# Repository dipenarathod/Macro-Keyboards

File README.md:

# Macro-Keyboards
Pending and completed macro keyboards:
1)Macro Keyboard: Pending, uses Atmega 32u4
2)MacroKeyboard2: Completed, uses push-buttons
3)MacroKeyboard2RotaryEncoders_Mech_with_profiles: Completed, uses LEDs for profiles and has Cherry MX switches
4)MacroKeyboardOLED: PCB pending, will have Cherry MX switches and an SSD1306
5)ModdedCrown.pretty: Crown logo for PCB

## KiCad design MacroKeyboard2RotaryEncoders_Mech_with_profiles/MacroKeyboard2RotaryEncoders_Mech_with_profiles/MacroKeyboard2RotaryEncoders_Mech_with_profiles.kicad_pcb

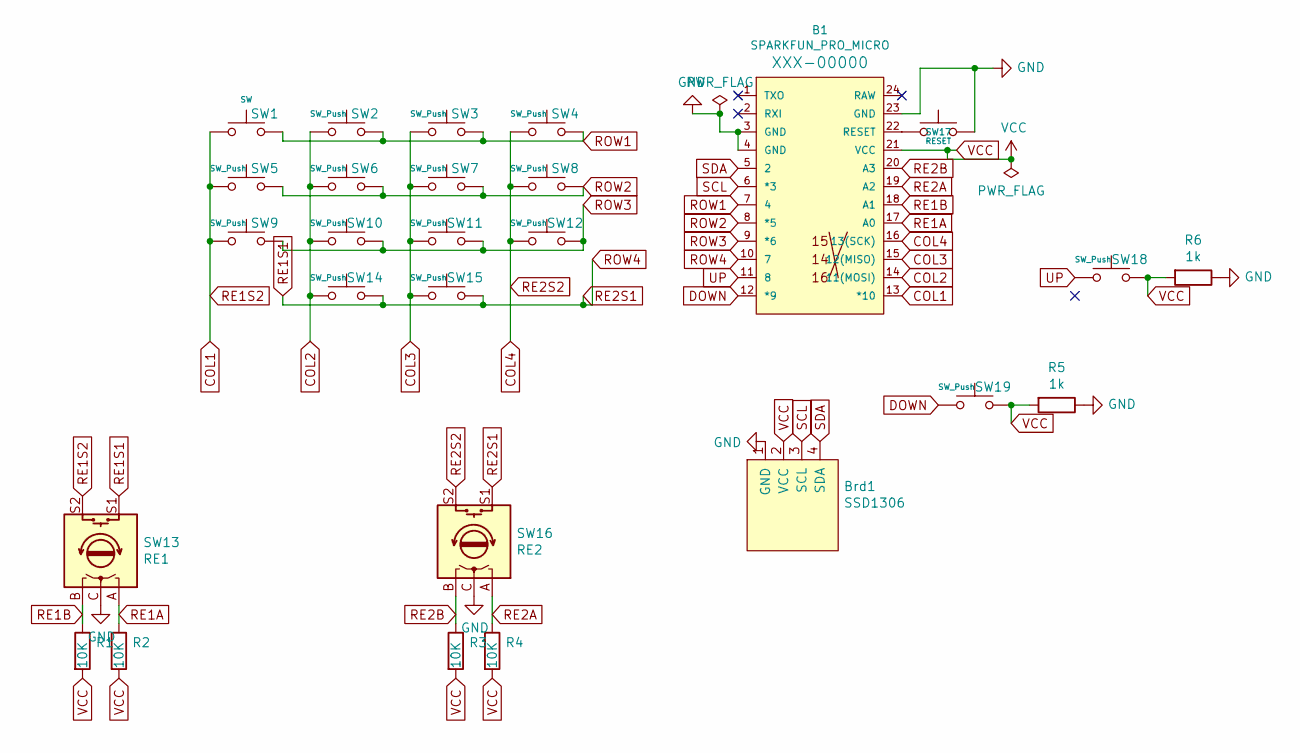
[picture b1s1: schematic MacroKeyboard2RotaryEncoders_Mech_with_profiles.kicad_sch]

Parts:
B1: SPARKFUN_PRO_MICRO
Brd1: SSD1306; 128x64OLED
R1, R2, R3, R4: 10K; R_Axial_DIN0204_L3.6mm_D1.6mm_P5.08mm_Horizontal
R5, R6: 1k; R_Axial_DIN0204_L3.6mm_D1.6mm_P5.08mm_Horizontal
SW1: SW; SW_Cherry_MX_1.00u_Plate
SW2, SW3, SW4, SW5, SW6, SW7, SW8, SW9, SW10, SW11, SW12, SW14, SW15: SW_Push; SW_Cherry_MX_1.00u_Plate
SW13: RE1; RotaryEncoder_Alps_EC11E-Switch_Vertical_H20mm
SW16: RE2; RotaryEncoder_Alps_EC11E-Switch_Vertical_H20mm
SW17: RESET; SW_PUSH_6mm_H4.3mm
SW18, SW19: SW_Push; SW_PUSH_6mm_H4.3mm

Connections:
COL1: B1.13 (*10), SW1.1, SW5.1, SW9.1, SW13.S2
COL2: B1.14 (11(MOSI)), SW2.1, SW6.1, SW10.1, SW14.1
COL3: B1.15 (12(MISO)), SW3.1, SW7.1, SW11.1, SW15.1
COL4: B1.16 (13(SCK)), SW4.1, SW8.1, SW12.1, SW16.S2
DOWN: B1.12 (*9), SW19.1
GND: B1.3 (GND), B1.4 (GND), B1.23 (GND), Brd1.1 (GND), R5.1, R6.1, SW13.C, SW16.C, SW17.2
unnamed: B1.22 (RESET), SW17.1
RE1A: B1.17 (A0), R2.1, SW13.A
RE1B: B1.18 (A1), R1.1, SW13.B
RE1S1: B1.10 (7), SW13.S1, SW14.2, SW15.2, SW16.S1
RE2A: B1.19 (A2), R4.1, SW16.A
RE2B: B1.20 (A3), R3.1, SW16.B
ROW1: B1.7 (4), SW1.2, SW2.2, SW3.2, SW4.2
ROW2: B1.8 (*5), SW5.2, SW6.2, SW7.2, SW8.2
ROW3: B1.9 (*6), SW9.2, SW10.2, SW11.2, SW12.2
SCL: B1.6 (*3), Brd1.3 (SCL)
SDA: B1.5 (2), Brd1.4 (SDA)
UP: B1.11 (8), SW18.1
VCC: B1.21 (VCC), Brd1.2 (VCC), R1.2, R2.2, R3.2, R4.2, R5.2, R6.2, SW18.2, SW19.2

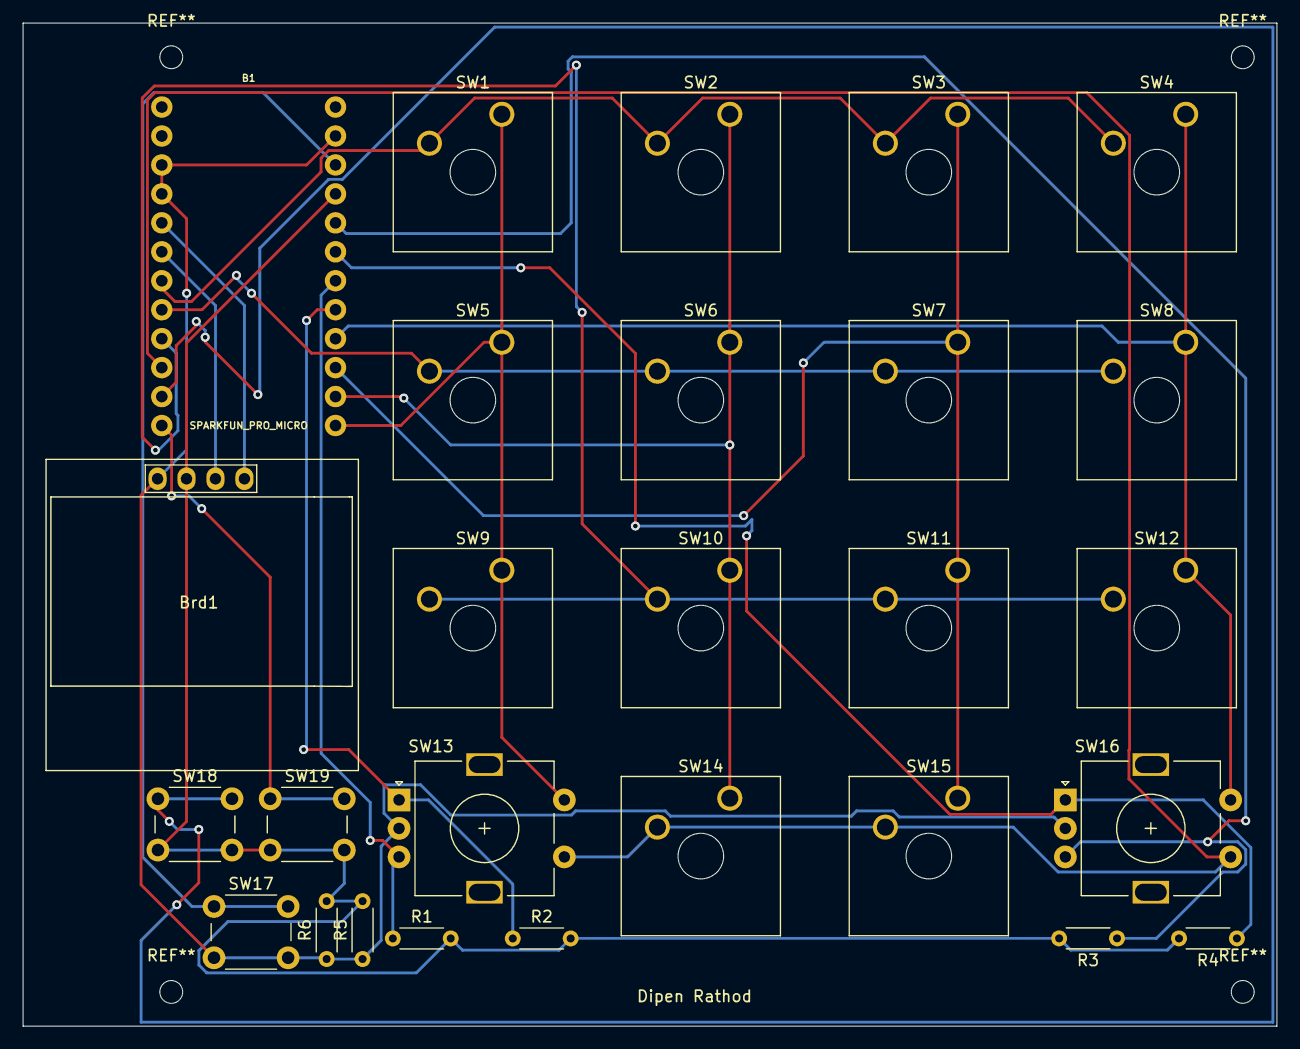
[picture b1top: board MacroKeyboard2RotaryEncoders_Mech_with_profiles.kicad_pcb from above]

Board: 2 copper layers, 110.0 x 88.0 mm, 27 parts (0 on the bottom side), 19 nets.

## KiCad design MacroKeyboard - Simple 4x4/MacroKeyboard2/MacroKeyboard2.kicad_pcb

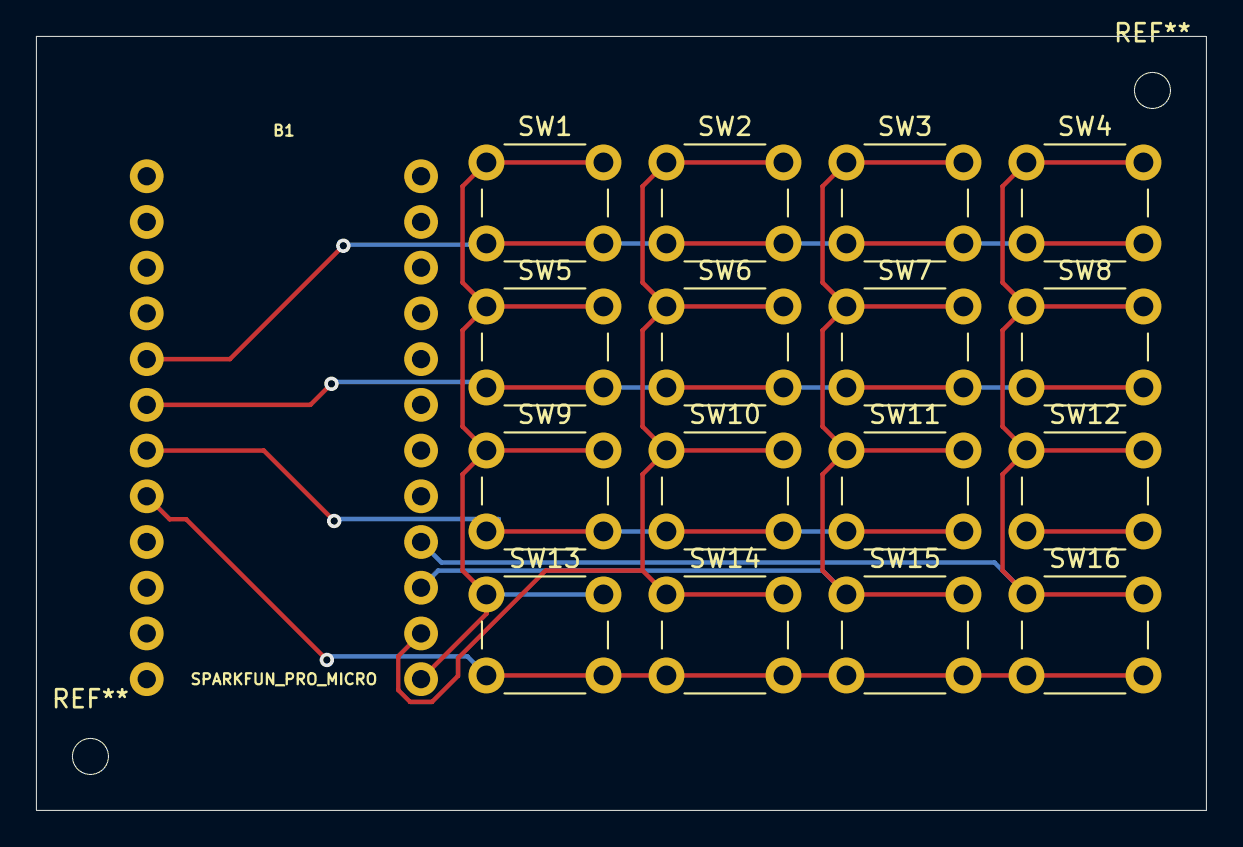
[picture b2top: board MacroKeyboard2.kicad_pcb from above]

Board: 2 copper layers, 65.0 x 43.0 mm, 17 parts (0 on the bottom side), 8 nets.

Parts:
B1: SPARKFUN_PRO_MICRO
SW1: SW; SW_PUSH_6mm_H4.3mm
SW2, SW3, SW4, SW5, SW6, SW7, SW8, SW9, SW10, SW11, SW12, SW13, SW14, SW15, SW16: SW_Push; SW_PUSH_6mm_H4.3mm

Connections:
unnamed: B1.5, SW1.2, SW2.2, SW3.2, SW4.2
unnamed: B1.6, SW5.2, SW6.2, SW7.2, SW8.2
unnamed: B1.7, SW9.2, SW10.2, SW11.2, SW12.2
unnamed: B1.8, SW13.2, SW14.2, SW15.2, SW16.2
unnamed: B1.13, SW1.1, SW5.1, SW9.1, SW13.1
unnamed: B1.14, SW2.1, SW6.1, SW10.1, SW14.1
unnamed: B1.15, SW3.1, SW7.1, SW11.1, SW15.1
unnamed: B1.16, SW4.1, SW8.1, SW12.1, SW16.1

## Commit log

2021-04-18 Add files via upload
    Macro Keyboard: Pending, uses Atmega 32u4
    MacroKeyboard2: Completed, uses push-buttons
    MacroKeyboard2RotaryEncoders_Mech_with_profiles: Completed, uses LEDs for profiles and has Cherry MX switches
    MacroKeyboardOLED: PCB pending, will have Cherry MX switches and an SSD1306
    ModdedCrown.pretty: Crown logo for PCB
2025-05-20 Updated Structure
